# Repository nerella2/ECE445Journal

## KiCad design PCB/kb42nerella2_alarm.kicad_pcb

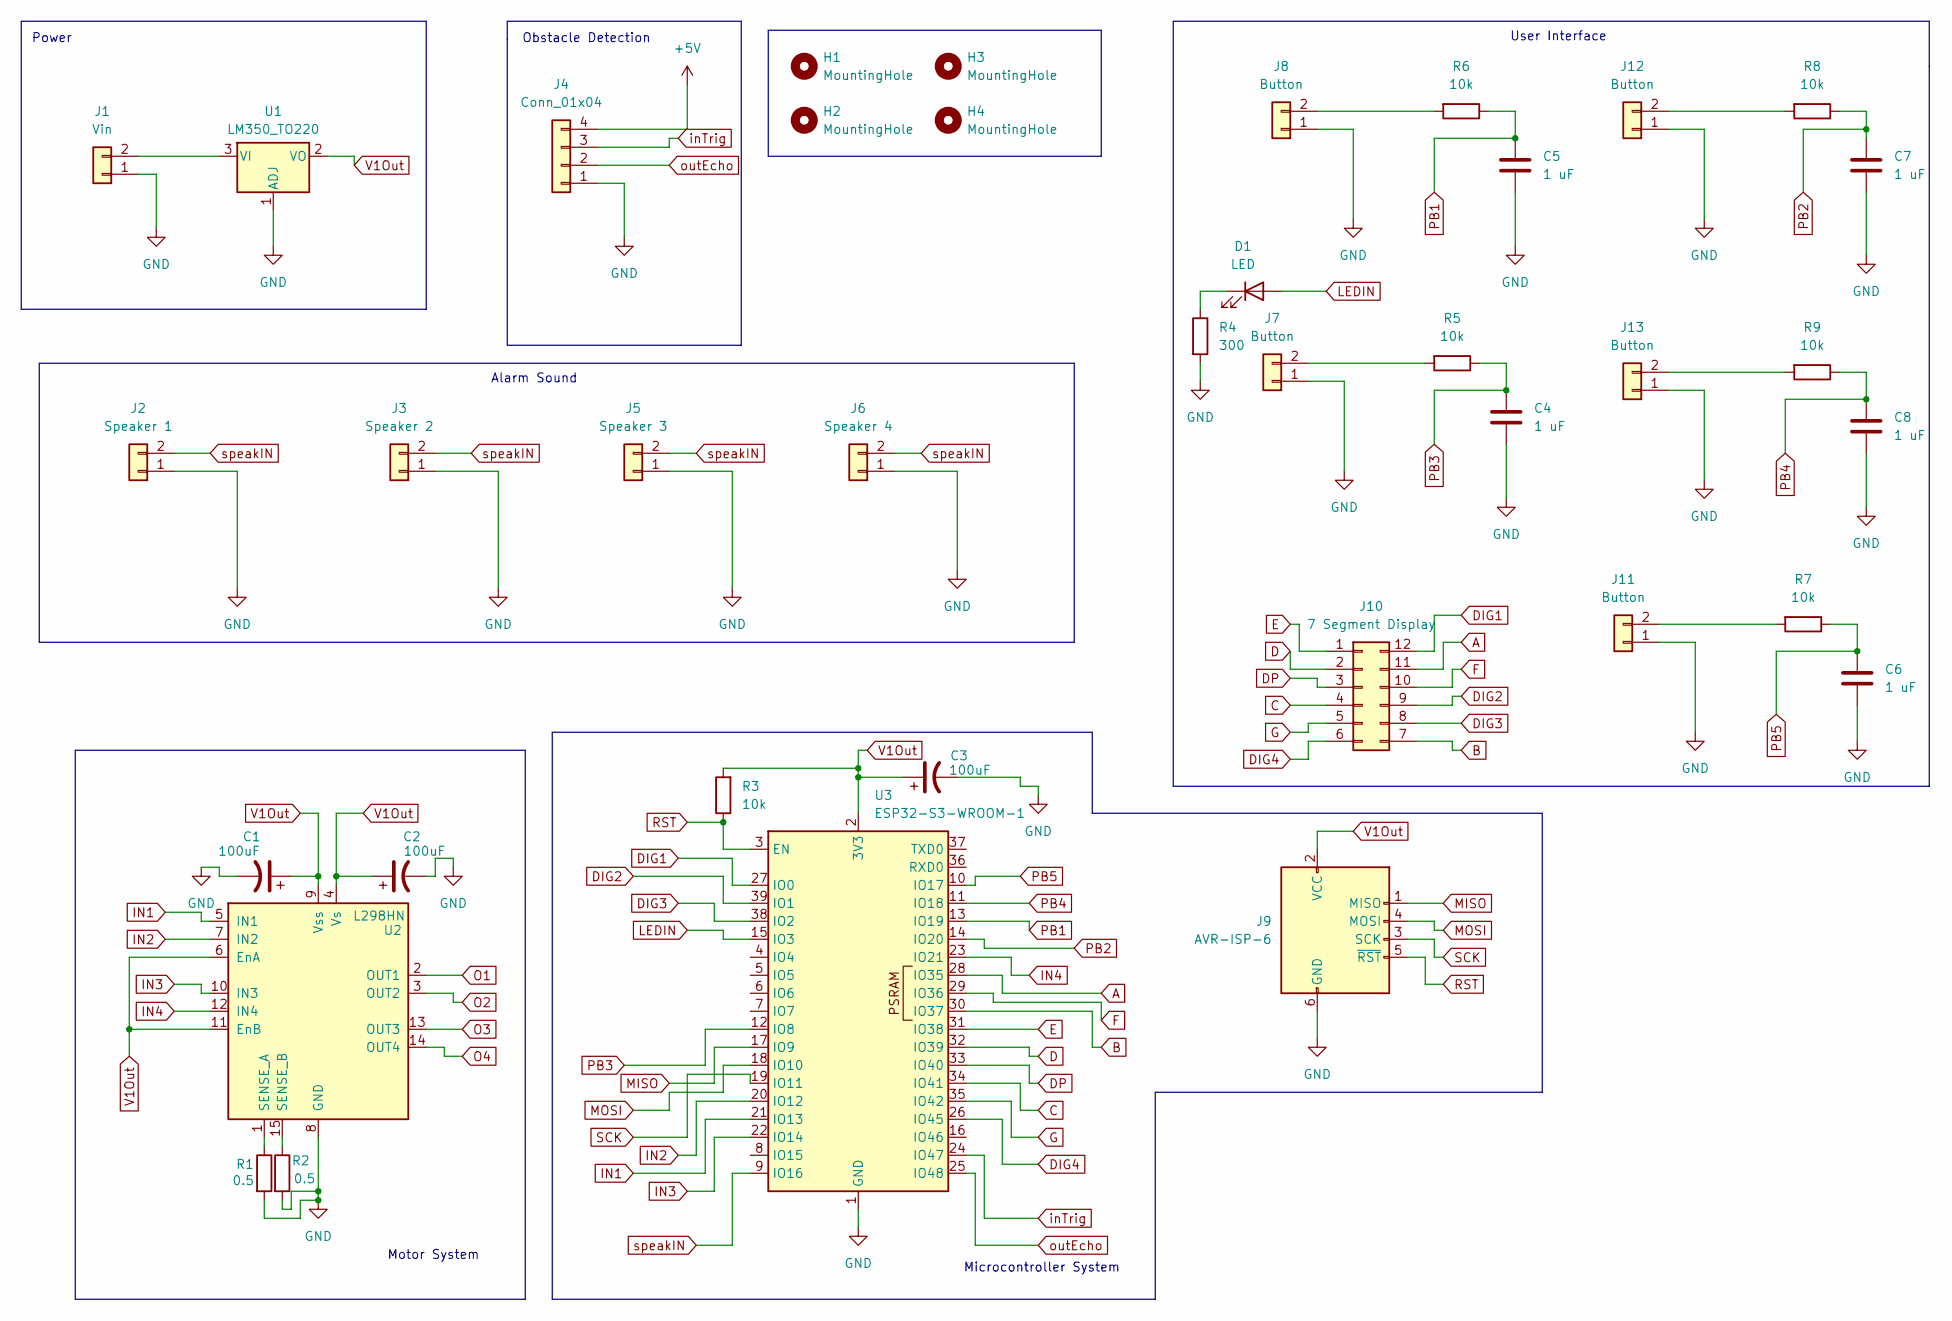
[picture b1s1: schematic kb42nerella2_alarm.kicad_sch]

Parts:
C1, C2, C3: 100uF; C_0805_2012Metric_Pad1.18x1.45mm_HandSolder
C4, C5, C6, C7, C8: 1 uF; C_0805_2012Metric_Pad1.18x1.45mm_HandSolder
D1: LED; Molex_KK-254_AE-6410-02A_1x02_P2.54mm_Vertical
H1, H2, H3, H4: MountingHole; MountingHole_3.2mm_M3
J1: Vin; Molex_KK-254_AE-6410-02A_1x02_P2.54mm_Vertical
J2: Speaker 1; Molex_KK-254_AE-6410-02A_1x02_P2.54mm_Vertical
J3: Speaker 2; Molex_KK-254_AE-6410-02A_1x02_P2.54mm_Vertical
J4: Conn_01x04; Molex_KK-254_AE-6410-04A_1x04_P2.54mm_Vertical
J5: Speaker 3; Molex_KK-254_AE-6410-02A_1x02_P2.54mm_Vertical
J6: Speaker 4; Molex_KK-254_AE-6410-02A_1x02_P2.54mm_Vertical
J7, J8, J11, J12, J13: Button; Molex_KK-254_AE-6410-02A_1x02_P2.54mm_Vertical
J9: AVR-ISP-6; IDC-Header_2x03_P2.54mm_Vertical
J10: 7 Segment Display; IDC-Header_2x06_P2.54mm_Vertical
R1, R2: 0.5; R_0805_2012Metric_Pad1.20x1.40mm_HandSolder
R3, R5, R6, R7, R8, R9: 10k; R_0805_2012Metric_Pad1.20x1.40mm_HandSolder
R4: 300; R_0805_2012Metric_Pad1.20x1.40mm_HandSolder
U1: LM350_TO220; TO-220-3_Vertical
U2: L298HN; TO-220-15_P2.54x2.54mm_StaggerOdd_Lead5.84mm_TabDown
U3: ESP32-S3-WROOM-1

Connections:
+5V: J4.4
A: J10.11, U3.28 (IO35)
B: J10.7, U3.30 (IO37)
C: J10.4, U3.34 (IO41)
D: J10.2, U3.32 (IO39)
DIG1: J10.12, U3.27 (IO0)
DIG2: J10.9, U3.39 (IO1)
DIG3: J10.8, U3.38 (IO2)
DIG4: J10.6, U3.26 (IO45)
DP: J10.3, U3.33 (IO40)
E: J10.1, U3.31 (IO38)
F: J10.10, U3.29 (IO36)
G: J10.5, U3.35 (IO42)
GND: C1.2, C2.2, C3.2, C4.2, C5.2, C6.2, C7.2, C8.2, J1.1, J2.1, J3.1, J4.1, J5.1, J6.1, J7.1, J8.1, J9.6 (GND), J11.1, J12.1, J13.1, R1.2, R2.2, R4.2, U1.1 (ADJ), U2.8 (GND), U3.1 (GND), U3.40 (GND), U3.41 (GND)
IN1: U2.5 (IN1), U3.21 (IO13)
IN2: U2.7 (IN2), U3.20 (IO12)
IN3: U2.10 (IN3), U3.22 (IO14)
IN4: U2.12 (IN4), U3.23 (IO21)
LEDIN: D1.2 (A), U3.15 (IO3)
MISO: J9.1 (MISO), U3.17 (IO9)
MOSI: J9.4 (MOSI), U3.18 (IO10)
unnamed: D1.1 (K), R4.1
unnamed: J1.2, U1.3 (VI)
unnamed: J7.2, R5.2
unnamed: J8.2, R6.2
unnamed: J11.2, R7.2
unnamed: J12.2, R8.2
unnamed: J13.2, R9.2
unnamed: R1.1, U2.1 (SENSE_A)
unnamed: R2.1, U2.15 (SENSE_B)
O1: U2.2 (OUT1)
O2: U2.3 (OUT2)
O3: U2.13 (OUT3)
O4: U2.14 (OUT4)
PB1: C5.1, R6.1, U3.13 (IO19)
PB2: C7.1, R8.1, U3.14 (IO20)
PB3: C4.1, R5.1, U3.12 (IO8)
PB4: C8.1, R9.1, U3.11 (IO18)
PB5: C6.1, R7.1, U3.10 (IO17)
RST: J9.5 (~RST), R3.1, U3.3 (EN)
SCK: J9.3 (SCK), U3.19 (IO11)
V1Out: C1.1, C2.1, C3.1, J9.2 (VCC), R3.2, U1.2 (VO), U2.4 (Vs), U2.6 (EnA), U2.9 (Vss), U2.11 (EnB), U3.2 (3V3)
inTrig: J4.3, U3.24 (IO47)
outEcho: J4.2, U3.25 (IO48)
speakIN: J2.2, J3.2, J5.2, J6.2, U3.9 (IO16)

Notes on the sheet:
Alarm Sound
Microcontroller System
Motor System
User Interface
Power
Obstacle Detection

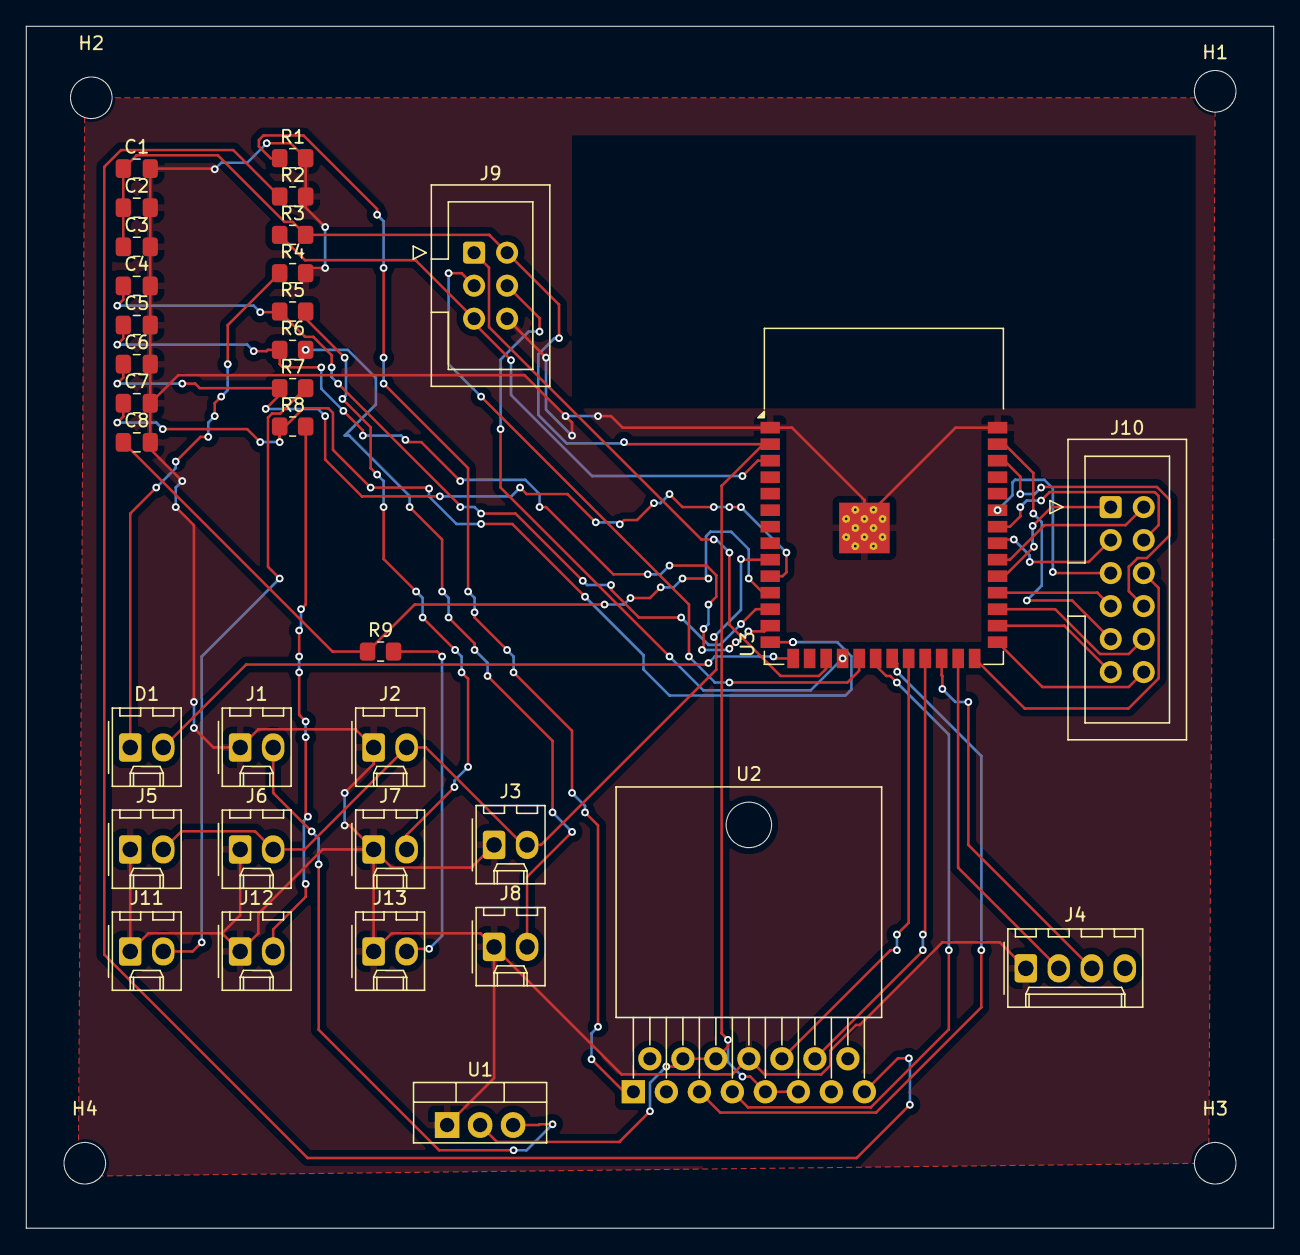
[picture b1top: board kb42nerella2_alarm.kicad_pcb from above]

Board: 2 copper layers, 96.0 x 92.5 mm, 38 parts (0 on the bottom side), 40 nets.

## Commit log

2024-09-17 Create empty
2024-09-30 Add files via upload
    Added Initial Project Proposal
2024-12-12 Add code
2024-12-12 Rename proposal2.pdf to ECE 445 Project Proposal Edit.pdf
